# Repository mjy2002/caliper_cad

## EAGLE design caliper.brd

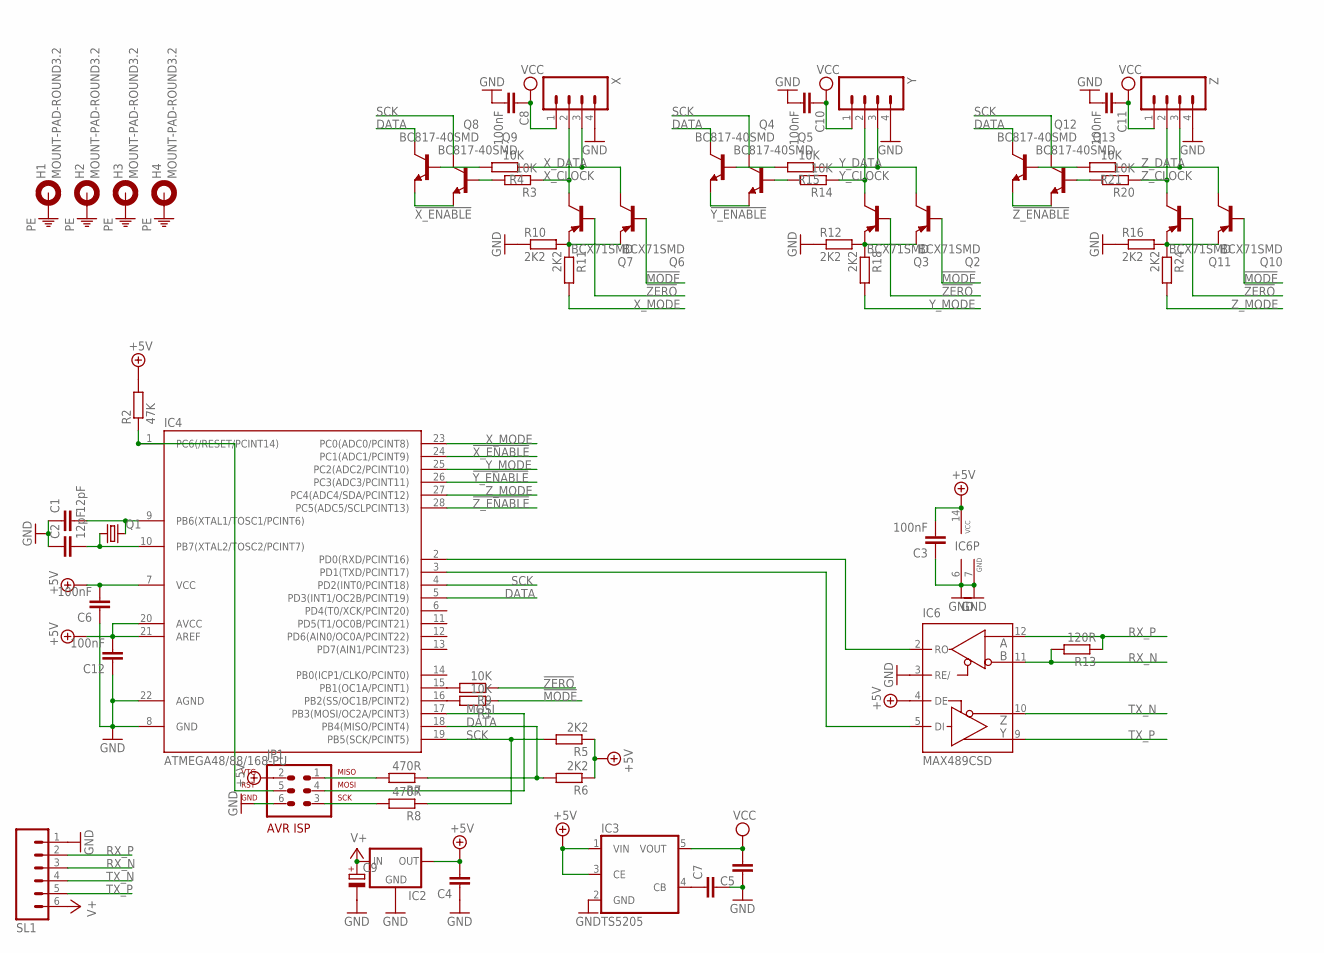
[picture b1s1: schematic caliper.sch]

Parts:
C1, C2: 12pF; C0805
C3, C6, C8, C10, C11, C12: 100nF; C0805
C4, C5, C7: C-EUC0805; C0805
C9: CPOL-EUE3.5-8; E3,5-8
H1, H2, H3, H4: MOUNT-PAD-ROUND3.2; 3,2-PAD
IC2: 78XXS
IC3: TS5205; SOT25
IC4: ATMEGA48/88/168-PU; DIL28-3
IC6: MAX489CSD; SO14
JP1: AVR-ISP-6
Q1: CRYTALHC49S; HC49/S
Q2, Q3, Q6, Q7, Q10, Q11: BCX71SMD; SOT23
Q4, Q5, Q8, Q9, Q12, Q13: BC817-40SMD; SOT23-BEC
R1, R3, R4, R9, R14, R15, R20, R21: 10K; R0805
R2: 47K; R0805
R5, R6, R10, R11, R12, R16, R18, R24: 2K2; R0805
R7, R8: 470R; R0805
R13: 120R; R0805
SL1: M06; 06P
X: M04; 04P
Y: M04; 04P
Z: M04; 04P

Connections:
!MODE: Q2.1 (B), Q6.1 (B), Q10.1 (B), R1.1
!X_ENABLE: IC4.24 (PC1(ADC1/PCINT9)), Q8.E, Q9.E
!Y_ENABLE: IC4.26 (PC3(ADC3/PCINT11)), Q4.E, Q5.E
!ZERO: Q3.1 (B), Q7.1 (B), Q11.1 (B), R9.1
!Z_ENABLE: IC4.28 (PC5(ADC5/SCLPCINT13)), Q12.E, Q13.E
+5V: C3.2, C4.2, C6.2, C12.2, IC2.OUT, IC3.1 (VIN), IC3.3 (CE), IC4.7 (VCC), IC4.20 (AVCC), IC4.21 (AREF), IC6.4 (DE), IC6.14 (VCC), JP1.2, R2.2, R5.1, R6.1
DATA: IC4.5 (PD3(INT1/OC2B/PCINT19)), IC4.18 (PB4(MISO/PCINT4)), Q4.C, Q8.C, Q12.C, R6.2, R7.1
GND: C1.1, C2.1, C3.1, C4.1, C5.1, C6.1, C7.2, C8.2, C9.-, C10.2, C11.2, C12.1, IC2.GND, IC3.2 (GND), IC4.8 (GND), IC4.22 (AGND), IC6.3 (RE/), IC6.6 (GND), IC6.7 (GND), JP1.6, R10.1, R12.1, R16.1, SL1.1, X.4, Y.4, Z.4
MOSI: IC4.17 (PB3(MOSI/OC2A/PCINT3)), JP1.4
unnamed: C1.2, IC4.9 (PB6(XTAL1/TOSC1/PCINT6)), Q1.2
unnamed: C2.2, IC4.10 (PB7(XTAL2/TOSC2/PCINT7)), Q1.1
unnamed: IC4.2 (PD0(RXD/PCINT16)), IC6.2 (RO)
unnamed: IC4.3 (PD1(TXD/PCINT17)), IC6.5 (DI)
unnamed: JP1.1, R7.2
unnamed: IC4.15 (PB1(OC1A/PCINT1)), R9.2
unnamed: IC4.1 (PC6(/RESET/PCINT14)), JP1.5, R2.1
unnamed: IC4.16 (PB2(SS/OC1B/PCINT2)), R1.2
unnamed: Q6.2 (E), Q7.2 (E), R10.2, R11.1
unnamed: C7.1, IC3.4 (CB)
unnamed: JP1.3, R8.2
unnamed: Q4.B, R15.2
unnamed: Q12.B, R21.2
unnamed: Q8.B, R4.2
unnamed: Q9.B, R3.2
unnamed: Q5.B, R14.2
unnamed: Q2.2 (E), Q3.2 (E), R12.2, R18.1
unnamed: Q13.B, R20.2
unnamed: Q10.2 (E), Q11.2 (E), R16.2, R24.1
PE: H1.B3,2, H2.B3,2, H3.B3,2, H4.B3,2
RX_N: IC6.11 (B), R13.2, SL1.3
RX_P: IC6.12 (A), R13.1, SL1.2
SCK: IC4.4 (PD2(INT0/PCINT18)), IC4.19 (PB5(SCK/PCINT5)), Q5.C, Q9.C, Q13.C, R5.2, R8.1
TX_N: IC6.10 (Z), SL1.4
TX_P: IC6.9 (Y), SL1.5
V+: C9.+, IC2.IN, SL1.6
VCC: C5.2, C8.1, C10.1, C11.1, IC3.5 (VOUT), X.1, Y.1, Z.1
X_CLOCK: Q7.3 (C), R3.1, X.2
X_DATA: Q6.3 (C), R4.1, X.3
X_MODE: IC4.23 (PC0(ADC0/PCINT8)), R11.2
Y_CLOCK: Q3.3 (C), R14.1, Y.2
Y_DATA: Q2.3 (C), R15.1, Y.3
Y_MODE: IC4.25 (PC2(ADC2/PCINT10)), R18.2
Z_CLOCK: Q11.3 (C), R20.1, Z.2
Z_DATA: Q10.3 (C), R21.1, Z.3
Z_MODE: IC4.27 (PC4(ADC4/SDA/PCINT12)), R24.2

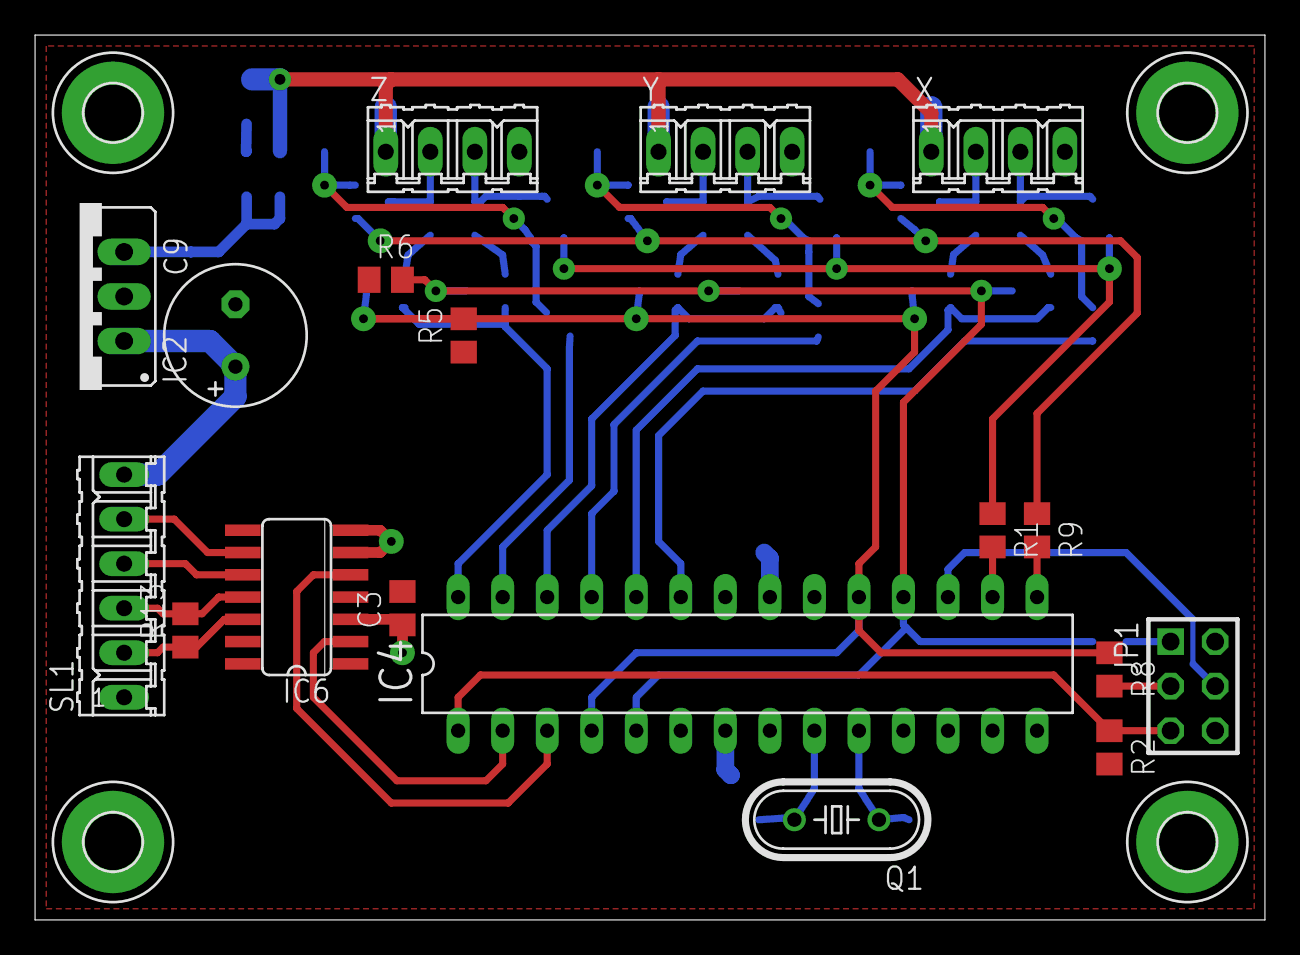
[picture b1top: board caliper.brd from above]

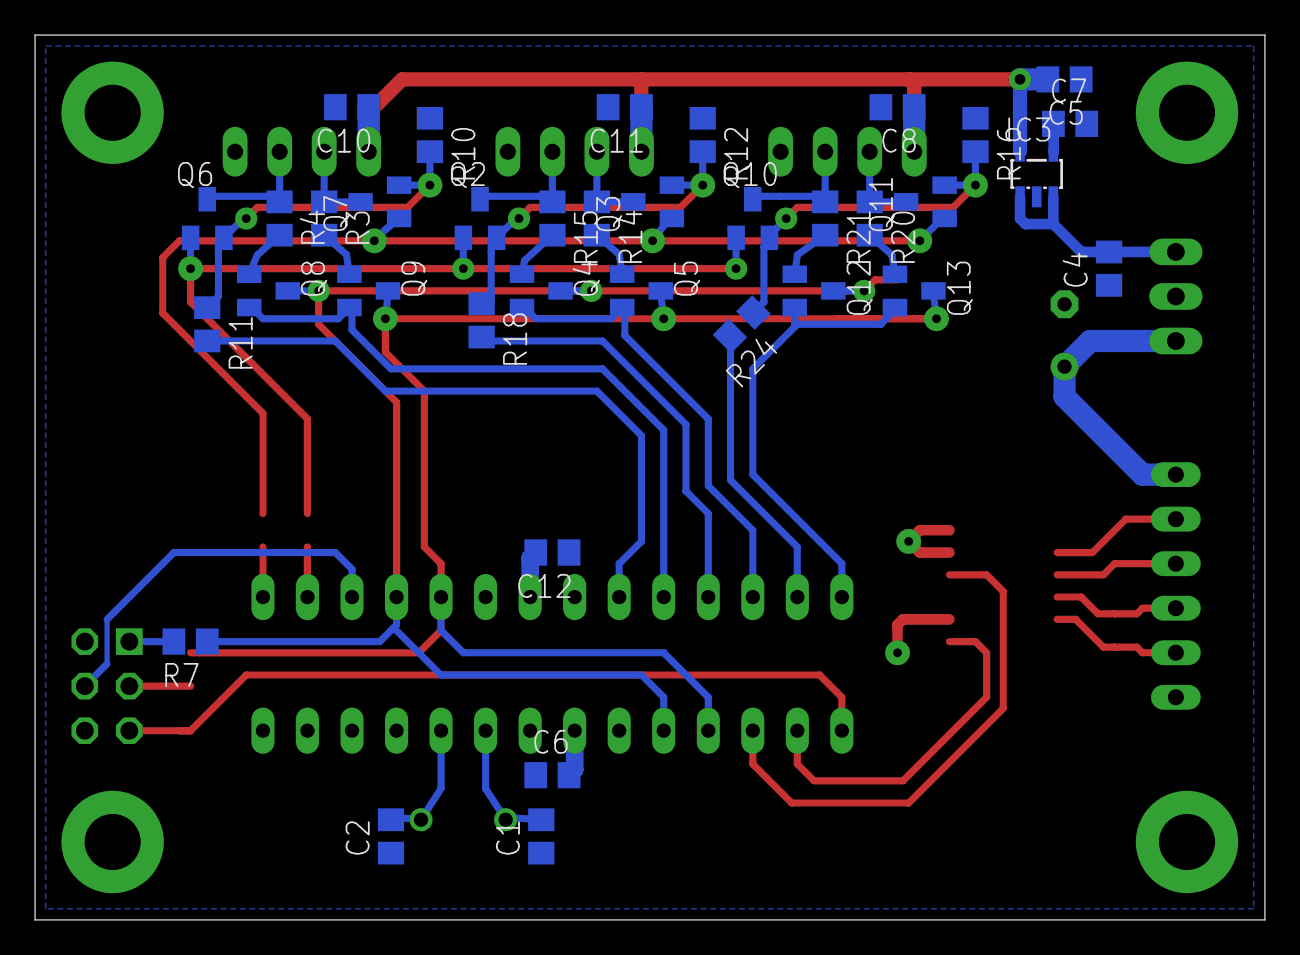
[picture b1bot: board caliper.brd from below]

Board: 2 copper layers, 70.1 x 50.5 mm, 58 parts (36 on the bottom side), 45 nets.

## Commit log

2017-11-28 erstes commit, platine auf basis Atiny2313 und spi fertig
2017-11-28 switch to ATmega88 & spi readout, Board & schematic ready
